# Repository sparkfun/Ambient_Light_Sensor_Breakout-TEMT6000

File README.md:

SparkFun Ambient Light Sensor Breakout Board - TEMT6000
=========================================================

[*SparkFun Ambient Light Sensor Breakout Board - TEMT6000 (BOB-08688)*](https://www.sparkfun.com/products/8688)

 Basic breakout board for the TEMT6000 Ambient Light Sensor.

Repository Contents
-------------------

* **/Hardware** - All Eagle design files (.brd, .sch)

Documentation
--------------

* **[Hookup Guide](https://learn.sparkfun.com/tutorials/temt6000-ambient-light-sensor-hookup-guide)** - Basic hookup guide.

License Information
-------------------
The hardware is released under [Creative Commons ShareAlike 4.0 International](https://creativecommons.org/licenses/by-sa/4.0/).

Distributed as-is; no warranty is given.

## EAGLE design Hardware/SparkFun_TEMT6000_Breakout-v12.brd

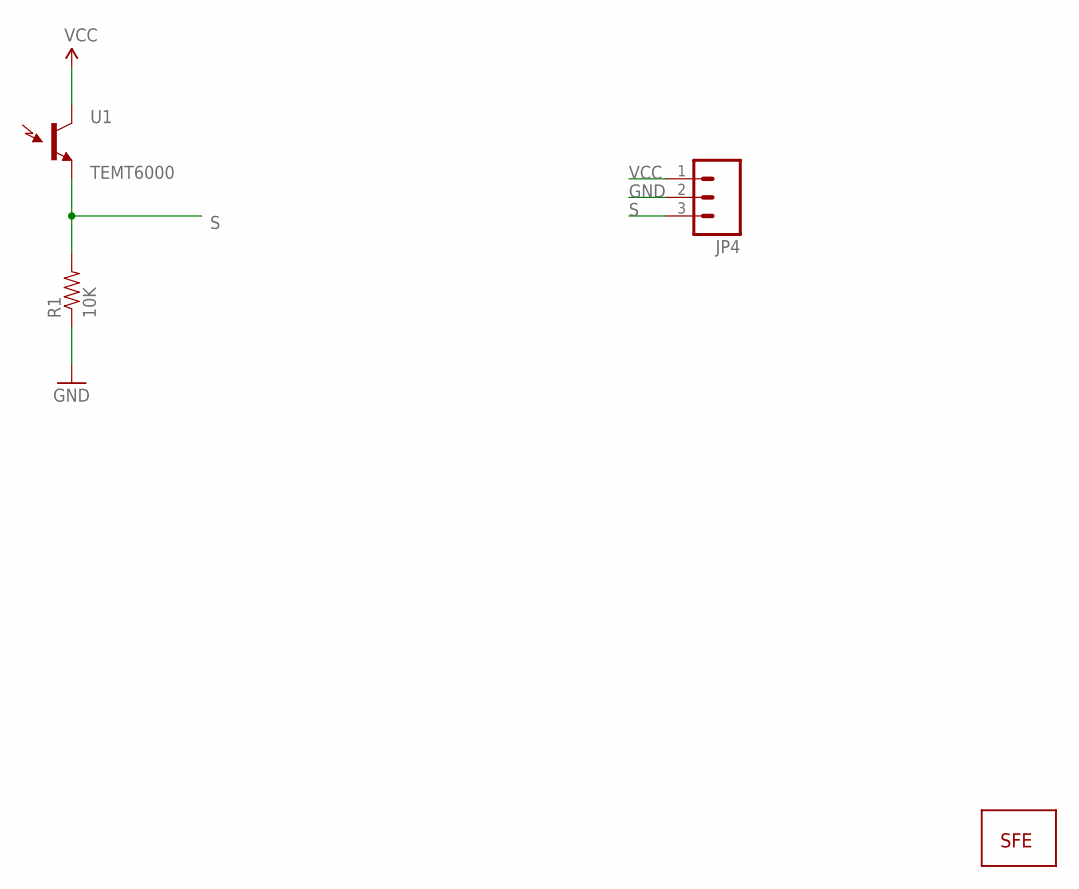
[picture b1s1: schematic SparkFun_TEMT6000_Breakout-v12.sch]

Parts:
JP4: M03PTH; 1X03
R1: 10K; 0402-RES
U1: TEMT6000; TEMT6000-SEN
U$1: LOGO-SFESK; SFE-LOGO-FLAME

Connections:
GND: JP4.2, R1.1
S: JP4.3, R1.2, U1.EMITTER (E1)
VCC: JP4.1, U1.COLLECTOR (C1)

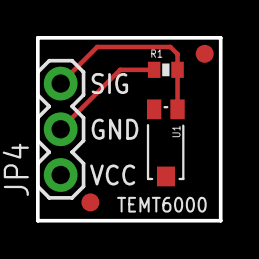
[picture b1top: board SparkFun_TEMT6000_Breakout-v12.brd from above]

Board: 2 copper layers, 10.2 x 10.2 mm, 6 parts (1 on the bottom side), 3 nets.

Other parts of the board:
E$1, E$2: FIDUCIAL-1X2

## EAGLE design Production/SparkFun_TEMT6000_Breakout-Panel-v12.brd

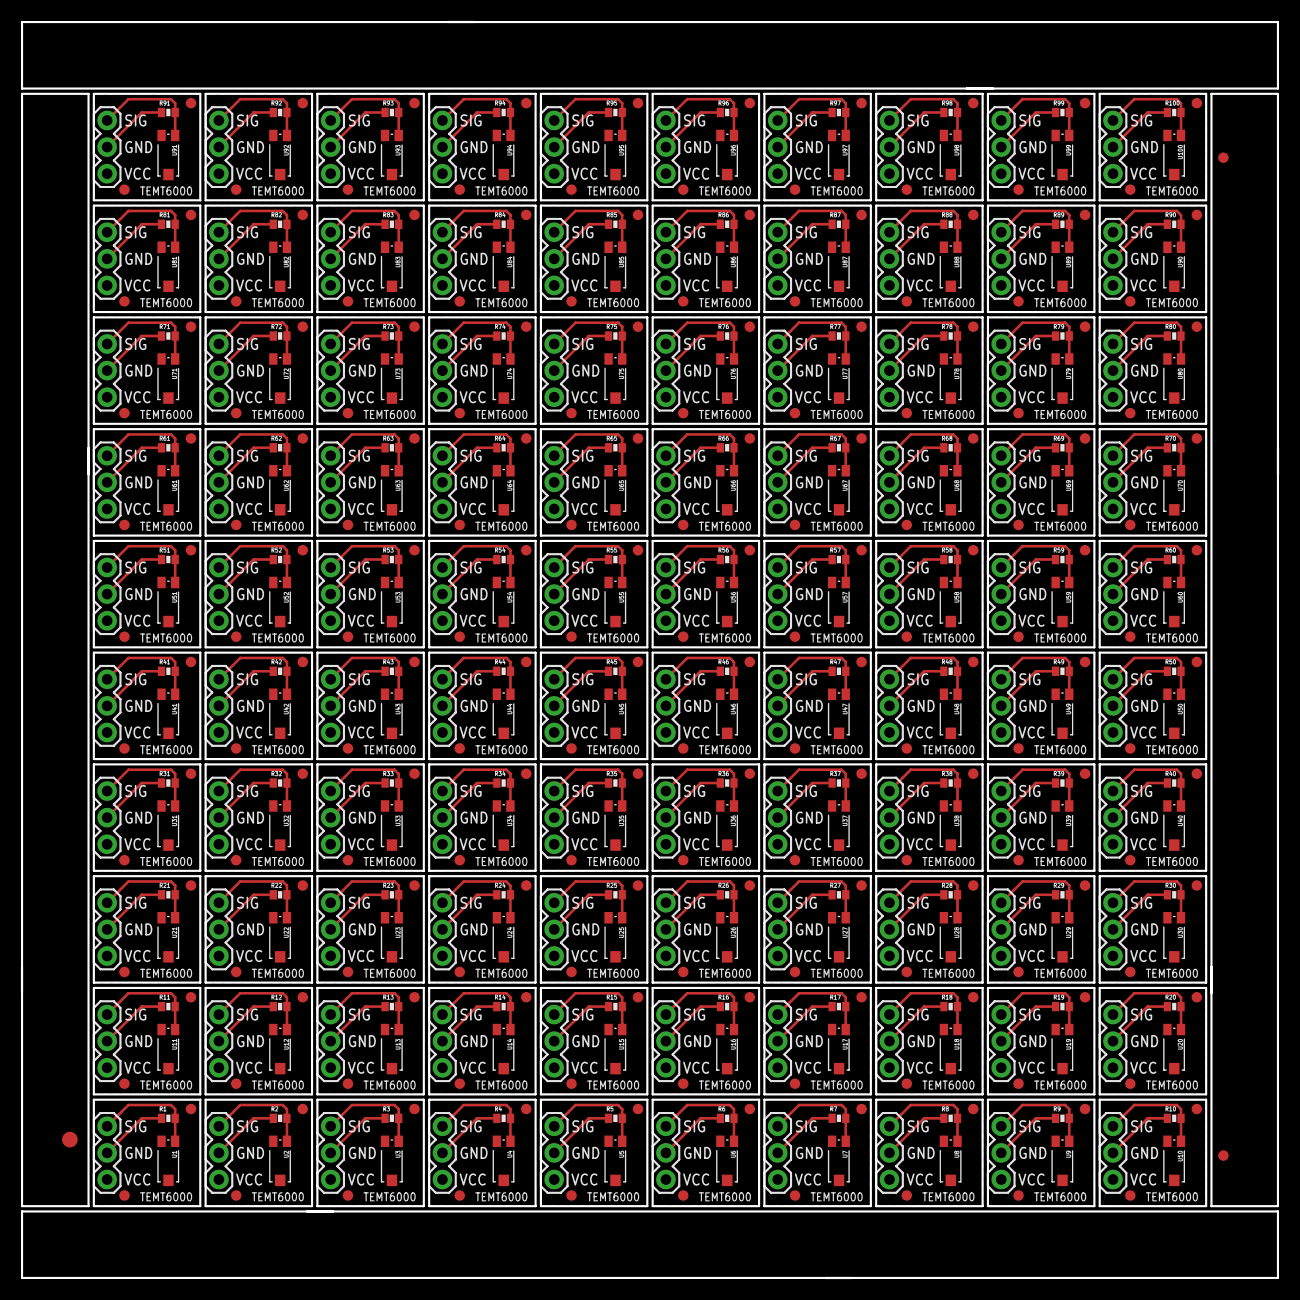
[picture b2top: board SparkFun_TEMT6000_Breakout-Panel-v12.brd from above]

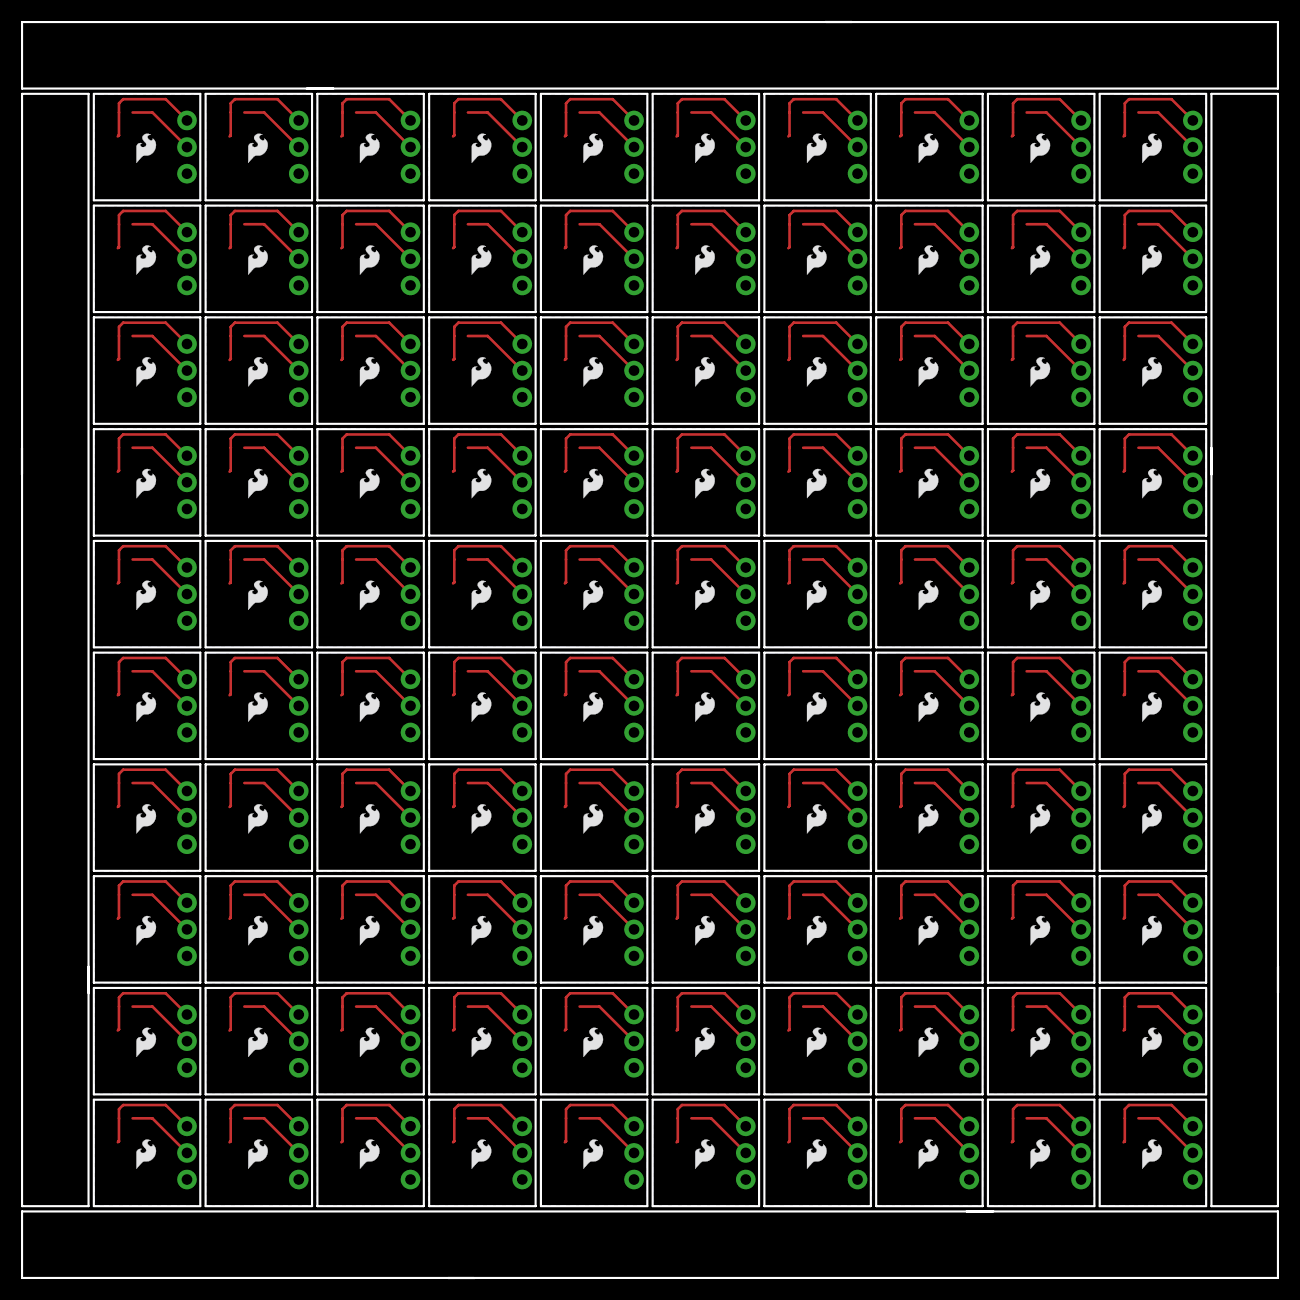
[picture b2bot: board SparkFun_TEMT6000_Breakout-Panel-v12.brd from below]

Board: 2 copper layers, 119.9 x 119.9 mm, 603 parts (100 on the bottom side), 300 nets.

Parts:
E$1, E$2, E$3, E$4, E$5, E$6, E$7, E$8, E$9, E$10, E$11, E$12, E$13, E$14, E$15, E$16, E$17, E$18, E$19, E$20, E$21, E$22, E$23, E$24, E$25, E$26, E$27, E$28, E$29, E$30, E$31, E$32, E$33, E$34, E$35, E$36, E$37, E$38, E$39, E$40, E$41, E$42, E$43, E$44, E$45, E$46, E$47, E$48, E$49, E$50, E$51, E$52, E$53, E$54, E$55, E$56, E$57, E$58, E$59, E$60, E$61, E$62, E$63, E$64, E$65, E$66, E$67, E$68, E$69, E$70, E$71, E$72, E$73, E$74, E$75, E$76, E$77, E$78, E$79, E$80, E$81, E$82, E$83, E$84, E$85, E$86, E$87, E$88, E$89, E$90, E$91, E$92, E$93, E$94, E$95, E$96, E$97, E$98, E$99, E$100, E$101, E$102, E$103, E$104, E$105, E$106, E$107, E$108, E$109, E$110, E$111, E$112, E$113, E$114, E$115, E$116, E$117, E$118, E$119, E$120, E$121, E$122, E$123, E$124, E$125, E$126, E$127, E$128, E$129, E$130, E$131, E$132, E$133, E$134, E$135, E$136, E$137, E$138, E$139, E$140, E$141, E$142, E$143, E$144, E$145, E$146, E$147, E$148, E$149, E$150, E$151, E$152, E$153, E$154, E$155, E$156, E$157, E$158, E$159, E$160, E$161, E$162, E$163, E$164, E$165, E$166, E$167, E$168, E$169, E$170, E$171, E$172, E$173, E$174, E$175, E$176, E$177, E$178, E$179, E$180, E$181, E$182, E$183, E$184, E$185, E$186, E$187, E$188, E$189, E$190, E$191, E$192, E$193, E$194, E$195, E$196, E$197, E$198, E$199, E$200, E$205, E$206: FIDUCIAL-1X2
E$201: FIDUCIAL-1.5X3
JP1, JP2, JP3, JP4, JP5, JP6, JP7, JP8, JP9, JP10, JP11, JP12, JP13, JP14, JP15, JP16, JP17, JP18, JP19, JP20, JP21, JP22, JP23, JP24, JP25, JP26, JP27, JP28, JP29, JP30, JP31, JP32, JP33, JP34, JP35, JP36, JP37, JP38, JP39, JP40, JP41, JP42, JP43, JP44, JP45, JP46, JP47, JP48, JP49, JP50, JP51, JP52, JP53, JP54, JP55, JP56, JP57, JP58, JP59, JP60, JP61, JP62, JP63, JP64, JP65, JP66, JP67, JP68, JP69, JP70, JP71, JP72, JP73, JP74, JP75, JP76, JP77, JP78, JP79, JP80, JP81, JP82, JP83, JP84, JP85, JP86, JP87, JP88, JP89, JP90, JP91, JP92, JP93, JP94, JP95, JP96, JP97, JP98, JP99, JP100: 1X03
R1, R2, R3, R4, R5, R6, R7, R8, R9, R10, R11, R12, R13, R14, R15, R16, R17, R18, R19, R20, R21, R22, R23, R24, R25, R26, R27, R28, R29, R30, R31, R32, R33, R34, R35, R36, R37, R38, R39, R40, R41, R42, R43, R44, R45, R46, R47, R48, R49, R50, R51, R52, R53, R54, R55, R56, R57, R58, R59, R60, R61, R62, R63, R64, R65, R66, R67, R68, R69, R70, R71, R72, R73, R74, R75, R76, R77, R78, R79, R80, R81, R82, R83, R84, R85, R86, R87, R88, R89, R90, R91, R92, R93, R94, R95, R96, R97, R98, R99, R100: 10K; 0402-RES
U1, U2, U3, U4, U5, U6, U7, U8, U9, U10, U11, U12, U13, U14, U15, U16, U17, U18, U19, U20, U21, U22, U23, U24, U25, U26, U27, U28, U29, U30, U31, U32, U33, U34, U35, U36, U37, U38, U39, U40, U41, U42, U43, U44, U45, U46, U47, U48, U49, U50, U51, U52, U53, U54, U55, U56, U57, U58, U59, U60, U61, U62, U63, U64, U65, U66, U67, U68, U69, U70, U71, U72, U73, U74, U75, U76, U77, U78, U79, U80, U81, U82, U83, U84, U85, U86, U87, U88, U89, U90, U91, U92, U93, U94, U95, U96, U97, U98, U99, U100: TEMT6000; TEMT6000-SEN
U$1, U$2, U$3, U$4, U$5, U$6, U$7, U$8, U$9, U$10, U$11, U$12, U$13, U$14, U$15, U$16, U$17, U$18, U$19, U$20, U$21, U$22, U$23, U$24, U$25, U$26, U$27, U$28, U$29, U$30, U$31, U$32, U$33, U$34, U$35, U$36, U$37, U$38, U$39, U$40, U$41, U$42, U$43, U$44, U$45, U$46, U$47, U$48, U$49, U$50, U$51, U$52, U$53, U$54, U$55, U$56, U$57, U$58, U$59, U$60, U$61, U$62, U$63, U$64, U$65, U$66, U$67, U$68, U$69, U$70, U$71, U$72, U$73, U$74, U$75, U$76, U$77, U$78, U$79, U$80, U$81, U$82, U$83, U$84, U$85, U$86, U$87, U$88, U$89, U$90, U$91, U$92, U$93, U$94, U$95, U$96, U$97, U$98, U$99, U$100: LOGO-SFESK; SFE-LOGO-FLAME

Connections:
GND: JP4.2, R1.1
GND1: JP1.2, R2.1
GND2: JP2.2, R3.1
GND3: JP3.2, R4.1
GND4: JP5.2, R5.1
GND5: JP6.2, R6.1
GND6: JP7.2, R7.1
GND7: JP8.2, R8.1
GND8: JP9.2, R9.1
GND9: JP10.2, R10.1
GND10: JP11.2, R11.1
GND11: JP12.2, R12.1
GND12: JP13.2, R13.1
GND13: JP14.2, R14.1
GND14: JP15.2, R15.1
GND15: JP16.2, R16.1
GND16: JP17.2, R17.1
GND17: JP18.2, R18.1
GND18: JP19.2, R19.1
GND19: JP20.2, R20.1
GND20: JP21.2, R21.1
GND21: JP22.2, R22.1
GND22: JP23.2, R23.1
GND23: JP24.2, R24.1
GND24: JP25.2, R25.1
GND25: JP26.2, R26.1
GND26: JP27.2, R27.1
GND27: JP28.2, R28.1
GND28: JP29.2, R29.1
GND29: JP30.2, R30.1
GND30: JP31.2, R31.1
GND31: JP32.2, R32.1
GND32: JP33.2, R33.1
GND33: JP34.2, R34.1
GND34: JP35.2, R35.1
GND35: JP36.2, R36.1
GND36: JP37.2, R37.1
GND37: JP38.2, R38.1
GND38: JP39.2, R39.1
GND39: JP40.2, R40.1
GND40: JP41.2, R41.1
GND41: JP42.2, R42.1
GND42: JP43.2, R43.1
GND43: JP44.2, R44.1
GND44: JP45.2, R45.1
GND45: JP46.2, R46.1
GND46: JP47.2, R47.1
GND47: JP48.2, R48.1
GND48: JP49.2, R49.1
GND49: JP50.2, R50.1
GND50: JP51.2, R51.1
GND51: JP52.2, R52.1
GND52: JP53.2, R53.1
GND53: JP54.2, R54.1
GND54: JP55.2, R55.1
GND55: JP56.2, R56.1
GND56: JP57.2, R57.1
GND57: JP58.2, R58.1
GND58: JP59.2, R59.1
GND59: JP60.2, R60.1
GND60: JP61.2, R61.1
GND61: JP62.2, R62.1
GND62: JP63.2, R63.1
GND63: JP64.2, R64.1
GND64: JP65.2, R65.1
GND65: JP66.2, R66.1
GND66: JP67.2, R67.1
GND67: JP68.2, R68.1
GND68: JP69.2, R69.1
GND69: JP70.2, R70.1
GND70: JP71.2, R71.1
GND71: JP72.2, R72.1
GND72: JP73.2, R73.1
GND73: JP74.2, R74.1
GND74: JP75.2, R75.1
GND75: JP76.2, R76.1
GND76: JP77.2, R77.1
GND77: JP78.2, R78.1
GND78: JP79.2, R79.1
GND79: JP80.2, R80.1
GND80: JP81.2, R81.1
GND81: JP82.2, R82.1
GND82: JP83.2, R83.1
GND83: JP84.2, R84.1
GND84: JP85.2, R85.1
GND85: JP86.2, R86.1
GND86: JP87.2, R87.1
GND87: JP88.2, R88.1
GND88: JP89.2, R89.1
GND89: JP90.2, R90.1
GND90: JP91.2, R91.1
GND91: JP92.2, R92.1
GND92: JP93.2, R93.1
GND93: JP94.2, R94.1
GND94: JP95.2, R95.1
GND95: JP96.2, R96.1
GND96: JP97.2, R97.1
GND97: JP98.2, R98.1
GND98: JP99.2, R99.1
GND99: JP100.2, R100.1
S: JP4.3, R1.2, U1.EMITTER
S1: JP1.3, R2.2, U2.EMITTER
S2: JP2.3, R3.2, U3.EMITTER
S3: JP3.3, R4.2, U4.EMITTER
S4: JP5.3, R5.2, U5.EMITTER
S5: JP6.3, R6.2, U6.EMITTER
S6: JP7.3, R7.2, U7.EMITTER
S7: JP8.3, R8.2, U8.EMITTER
S8: JP9.3, R9.2, U9.EMITTER
S9: JP10.3, R10.2, U10.EMITTER
S10: JP11.3, R11.2, U11.EMITTER
S11: JP12.3, R12.2, U12.EMITTER
S12: JP13.3, R13.2, U13.EMITTER
S13: JP14.3, R14.2, U14.EMITTER
S14: JP15.3, R15.2, U15.EMITTER
S15: JP16.3, R16.2, U16.EMITTER
S16: JP17.3, R17.2, U17.EMITTER
S17: JP18.3, R18.2, U18.EMITTER
S18: JP19.3, R19.2, U19.EMITTER
S19: JP20.3, R20.2, U20.EMITTER
S20: JP21.3, R21.2, U21.EMITTER
S21: JP22.3, R22.2, U22.EMITTER
S22: JP23.3, R23.2, U23.EMITTER
S23: JP24.3, R24.2, U24.EMITTER
S24: JP25.3, R25.2, U25.EMITTER
S25: JP26.3, R26.2, U26.EMITTER
S26: JP27.3, R27.2, U27.EMITTER
S27: JP28.3, R28.2, U28.EMITTER
S28: JP29.3, R29.2, U29.EMITTER
S29: JP30.3, R30.2, U30.EMITTER
S30: JP31.3, R31.2, U31.EMITTER
S31: JP32.3, R32.2, U32.EMITTER
S32: JP33.3, R33.2, U33.EMITTER
S33: JP34.3, R34.2, U34.EMITTER
S34: JP35.3, R35.2, U35.EMITTER
S35: JP36.3, R36.2, U36.EMITTER
S36: JP37.3, R37.2, U37.EMITTER
S37: JP38.3, R38.2, U38.EMITTER
S38: JP39.3, R39.2, U39.EMITTER
S39: JP40.3, R40.2, U40.EMITTER
S40: JP41.3, R41.2, U41.EMITTER
S41: JP42.3, R42.2, U42.EMITTER
S42: JP43.3, R43.2, U43.EMITTER
S43: JP44.3, R44.2, U44.EMITTER
S44: JP45.3, R45.2, U45.EMITTER
S45: JP46.3, R46.2, U46.EMITTER
S46: JP47.3, R47.2, U47.EMITTER
S47: JP48.3, R48.2, U48.EMITTER
S48: JP49.3, R49.2, U49.EMITTER
S49: JP50.3, R50.2, U50.EMITTER
S50: JP51.3, R51.2, U51.EMITTER
S51: JP52.3, R52.2, U52.EMITTER
S52: JP53.3, R53.2, U53.EMITTER
S53: JP54.3, R54.2, U54.EMITTER
S54: JP55.3, R55.2, U55.EMITTER
S55: JP56.3, R56.2, U56.EMITTER
S56: JP57.3, R57.2, U57.EMITTER
S57: JP58.3, R58.2, U58.EMITTER
S58: JP59.3, R59.2, U59.EMITTER
S59: JP60.3, R60.2, U60.EMITTER
S60: JP61.3, R61.2, U61.EMITTER
S61: JP62.3, R62.2, U62.EMITTER
S62: JP63.3, R63.2, U63.EMITTER
S63: JP64.3, R64.2, U64.EMITTER
S64: JP65.3, R65.2, U65.EMITTER
S65: JP66.3, R66.2, U66.EMITTER
S66: JP67.3, R67.2, U67.EMITTER
S67: JP68.3, R68.2, U68.EMITTER
S68: JP69.3, R69.2, U69.EMITTER
S69: JP70.3, R70.2, U70.EMITTER
S70: JP71.3, R71.2, U71.EMITTER
S71: JP72.3, R72.2, U72.EMITTER
S72: JP73.3, R73.2, U73.EMITTER
S73: JP74.3, R74.2, U74.EMITTER
S74: JP75.3, R75.2, U75.EMITTER
S75: JP76.3, R76.2, U76.EMITTER
S76: JP77.3, R77.2, U77.EMITTER
S77: JP78.3, R78.2, U78.EMITTER
S78: JP79.3, R79.2, U79.EMITTER
S79: JP80.3, R80.2, U80.EMITTER
S80: JP81.3, R81.2, U81.EMITTER
S81: JP82.3, R82.2, U82.EMITTER
S82: JP83.3, R83.2, U83.EMITTER
S83: JP84.3, R84.2, U84.EMITTER
S84: JP85.3, R85.2, U85.EMITTER
S85: JP86.3, R86.2, U86.EMITTER
S86: JP87.3, R87.2, U87.EMITTER
S87: JP88.3, R88.2, U88.EMITTER
S88: JP89.3, R89.2, U89.EMITTER
S89: JP90.3, R90.2, U90.EMITTER
S90: JP91.3, R91.2, U91.EMITTER
S91: JP92.3, R92.2, U92.EMITTER
S92: JP93.3, R93.2, U93.EMITTER
S93: JP94.3, R94.2, U94.EMITTER
S94: JP95.3, R95.2, U95.EMITTER
S95: JP96.3, R96.2, U96.EMITTER
S96: JP97.3, R97.2, U97.EMITTER
S97: JP98.3, R98.2, U98.EMITTER
S98: JP99.3, R99.2, U99.EMITTER
S99: JP100.3, R100.2, U100.EMITTER
VCC: JP4.1, U1.COLLECTOR
VCC1: JP1.1, U2.COLLECTOR
VCC2: JP2.1, U3.COLLECTOR
VCC3: JP3.1, U4.COLLECTOR
VCC4: JP5.1, U5.COLLECTOR
VCC5: JP6.1, U6.COLLECTOR
VCC6: JP7.1, U7.COLLECTOR
VCC7: JP8.1, U8.COLLECTOR
VCC8: JP9.1, U9.COLLECTOR
VCC9: JP10.1, U10.COLLECTOR
VCC10: JP11.1, U11.COLLECTOR
VCC11: JP12.1, U12.COLLECTOR
VCC12: JP13.1, U13.COLLECTOR
VCC13: JP14.1, U14.COLLECTOR
VCC14: JP15.1, U15.COLLECTOR
VCC15: JP16.1, U16.COLLECTOR
VCC16: JP17.1, U17.COLLECTOR
VCC17: JP18.1, U18.COLLECTOR
VCC18: JP19.1, U19.COLLECTOR
VCC19: JP20.1, U20.COLLECTOR
VCC20: JP21.1, U21.COLLECTOR
VCC21: JP22.1, U22.COLLECTOR
VCC22: JP23.1, U23.COLLECTOR
VCC23: JP24.1, U24.COLLECTOR
VCC24: JP25.1, U25.COLLECTOR
VCC25: JP26.1, U26.COLLECTOR
VCC26: JP27.1, U27.COLLECTOR
VCC27: JP28.1, U28.COLLECTOR
VCC28: JP29.1, U29.COLLECTOR
VCC29: JP30.1, U30.COLLECTOR
VCC30: JP31.1, U31.COLLECTOR
VCC31: JP32.1, U32.COLLECTOR
VCC32: JP33.1, U33.COLLECTOR
VCC33: JP34.1, U34.COLLECTOR
VCC34: JP35.1, U35.COLLECTOR
VCC35: JP36.1, U36.COLLECTOR
VCC36: JP37.1, U37.COLLECTOR
VCC37: JP38.1, U38.COLLECTOR
VCC38: JP39.1, U39.COLLECTOR
VCC39: JP40.1, U40.COLLECTOR
VCC40: JP41.1, U41.COLLECTOR
VCC41: JP42.1, U42.COLLECTOR
VCC42: JP43.1, U43.COLLECTOR
VCC43: JP44.1, U44.COLLECTOR
VCC44: JP45.1, U45.COLLECTOR
VCC45: JP46.1, U46.COLLECTOR
VCC46: JP47.1, U47.COLLECTOR
VCC47: JP48.1, U48.COLLECTOR
VCC48: JP49.1, U49.COLLECTOR
VCC49: JP50.1, U50.COLLECTOR
VCC50: JP51.1, U51.COLLECTOR
VCC51: JP52.1, U52.COLLECTOR
VCC52: JP53.1, U53.COLLECTOR
VCC53: JP54.1, U54.COLLECTOR
VCC54: JP55.1, U55.COLLECTOR
VCC55: JP56.1, U56.COLLECTOR
VCC56: JP57.1, U57.COLLECTOR
VCC57: JP58.1, U58.COLLECTOR
VCC58: JP59.1, U59.COLLECTOR
VCC59: JP60.1, U60.COLLECTOR
VCC60: JP61.1, U61.COLLECTOR
VCC61: JP62.1, U62.COLLECTOR
VCC62: JP63.1, U63.COLLECTOR
VCC63: JP64.1, U64.COLLECTOR
VCC64: JP65.1, U65.COLLECTOR
VCC65: JP66.1, U66.COLLECTOR
VCC66: JP67.1, U67.COLLECTOR
VCC67: JP68.1, U68.COLLECTOR
VCC68: JP69.1, U69.COLLECTOR
VCC69: JP70.1, U70.COLLECTOR
VCC70: JP71.1, U71.COLLECTOR
VCC71: JP72.1, U72.COLLECTOR
VCC72: JP73.1, U73.COLLECTOR
VCC73: JP74.1, U74.COLLECTOR
VCC74: JP75.1, U75.COLLECTOR
VCC75: JP76.1, U76.COLLECTOR
VCC76: JP77.1, U77.COLLECTOR
VCC77: JP78.1, U78.COLLECTOR
VCC78: JP79.1, U79.COLLECTOR
VCC79: JP80.1, U80.COLLECTOR
VCC80: JP81.1, U81.COLLECTOR
VCC81: JP82.1, U82.COLLECTOR
VCC82: JP83.1, U83.COLLECTOR
VCC83: JP84.1, U84.COLLECTOR
VCC84: JP85.1, U85.COLLECTOR
VCC85: JP86.1, U86.COLLECTOR
VCC86: JP87.1, U87.COLLECTOR
VCC87: JP88.1, U88.COLLECTOR
VCC88: JP89.1, U89.COLLECTOR
VCC89: JP90.1, U90.COLLECTOR
VCC90: JP91.1, U91.COLLECTOR
VCC91: JP92.1, U92.COLLECTOR
VCC92: JP93.1, U93.COLLECTOR
VCC93: JP94.1, U94.COLLECTOR
VCC94: JP95.1, U95.COLLECTOR
VCC95: JP96.1, U96.COLLECTOR
VCC96: JP97.1, U97.COLLECTOR
VCC97: JP98.1, U98.COLLECTOR
VCC98: JP99.1, U99.COLLECTOR
VCC99: JP100.1, U100.COLLECTOR

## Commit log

2015-03-03 Add hardware files, update README
2015-10-19 created panel v12

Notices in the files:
parts and their libraries:
SparkFun-Aesthetics: Licensing: CC v3.0 Share-Alike You are welcome to use this library for commercial purposes.
SparkFun-Retired: Licensing:Creative Commons ShareAlike 4.0 International - https://creativecommons.org/licenses/by-sa/4.0
